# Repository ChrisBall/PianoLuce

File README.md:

# PianoLuce

PianoLuce is a keypress detector for pianos, based on the Arduino platform. This project is on hiatus, having achieved it's main aim, but others trying to achieve similar results may find these resources useful.

This project took inspiration from the development on the [Magnetic Resonator Piano](http://www.eecs.qmul.ac.uk/~andrewm/mrp.html) and similar, commercial keypress detectors like the Moog Piano Bar.

Most of the development was in aid of a performance by Marta Mołodyńska-Wheeler in June 2017, where live visuals were generated from her PhD performance of Scriabin's 24 preludes. The vision of the project was to re-create a modern day version of [Clavier à lumières](https://en.wikipedia.org/wiki/Clavier_%C3%A0_lumi%C3%A8res) by creating a non-intrusive device which could be attached to an expensive piano and create colored visuals.  Alex (Marta's husband), CEO of the IOT company [Kolomolo](www.kolomolo.com), connected with me during his research and commissioned the work.

My special thanks to: [Alex & Marta](http://www.martamolo.com/), for their time, patience, and escape rooms; to [James Medd](http://jamesmedd.co.uk/) for his assistance designing a mounting system, and coming up with the name, PianoLuce; and to [Alexander Lang](http://langster1980.blogspot.co.uk/), for his usual excellent support.

## Description

PianoLuce uses side-mounted IR reflection detectors to estimate the velocity of keypresses. An IR reflection sensor (QRE1113) above each key measures reflected IR light. These sensors are switched on and read in sequence by an ATMEGA328P via 16 channel 4067 analog multiplexers. Each PCB spans an octave (12 notes), and boards communicate via I2C, although SPI may be possible. A master controller is responsible for controlling calibration, receiving keypress data from each slave board, getting data from a sustain pedal, and sending midi over USB.

## Resources
- [Arduino Code](https://github.com/ChrisBall/PianoLuce/tree/master/Arduino)
- [Eagle Files](https://github.com/ChrisBall/PianoLuce/tree/master/Eagle)
- [Mount design and cad files](https://github.com/ChrisBall/PianoLuce/tree/master/SVG)
- [Other Media](https://github.com/ChrisBall/PianoLuce/tree/master/Media)

## Flaws and possible improvements

As mentioned, PianoLuce is only partially developed, and there are many factors to consider in an improved future version. Please bear these points in mind before using this project as a basis for your own.
- Currently, keypresses on black keys are detected with ambient IR, which is obviously highly variable. More reliable measurement can be made by adding white stickers to each black key, and altering the current code to light the appropriate IR LED. A simpler to install system may use two reflection sensors to sense the void left by the black key when it is pressed.
- I2C is not designed for long range transmission: although the current system works (multi-slave setup), it may be susceptible to noise, and there is significant latency introduced by evaluating 7 slave boards. Improved data transmission between master and slaves should be implemented.
- The electronic design, while functional, could be simplified, made cheaper and smaller, and use a faster microcontroller from the STM32 series.
- The 10 pin IDC connectors chosen for board interconnects may disturb the performance of experienced pianists, particularly those with smaller hands as they will use the full length of each key. A lower profile interconnect would be ideal.
- There is no visual feedback: this was intentional, as it was deemed undesirable for our purposes, but in most cases it should be an option. LED feedback for each key is simple to add.

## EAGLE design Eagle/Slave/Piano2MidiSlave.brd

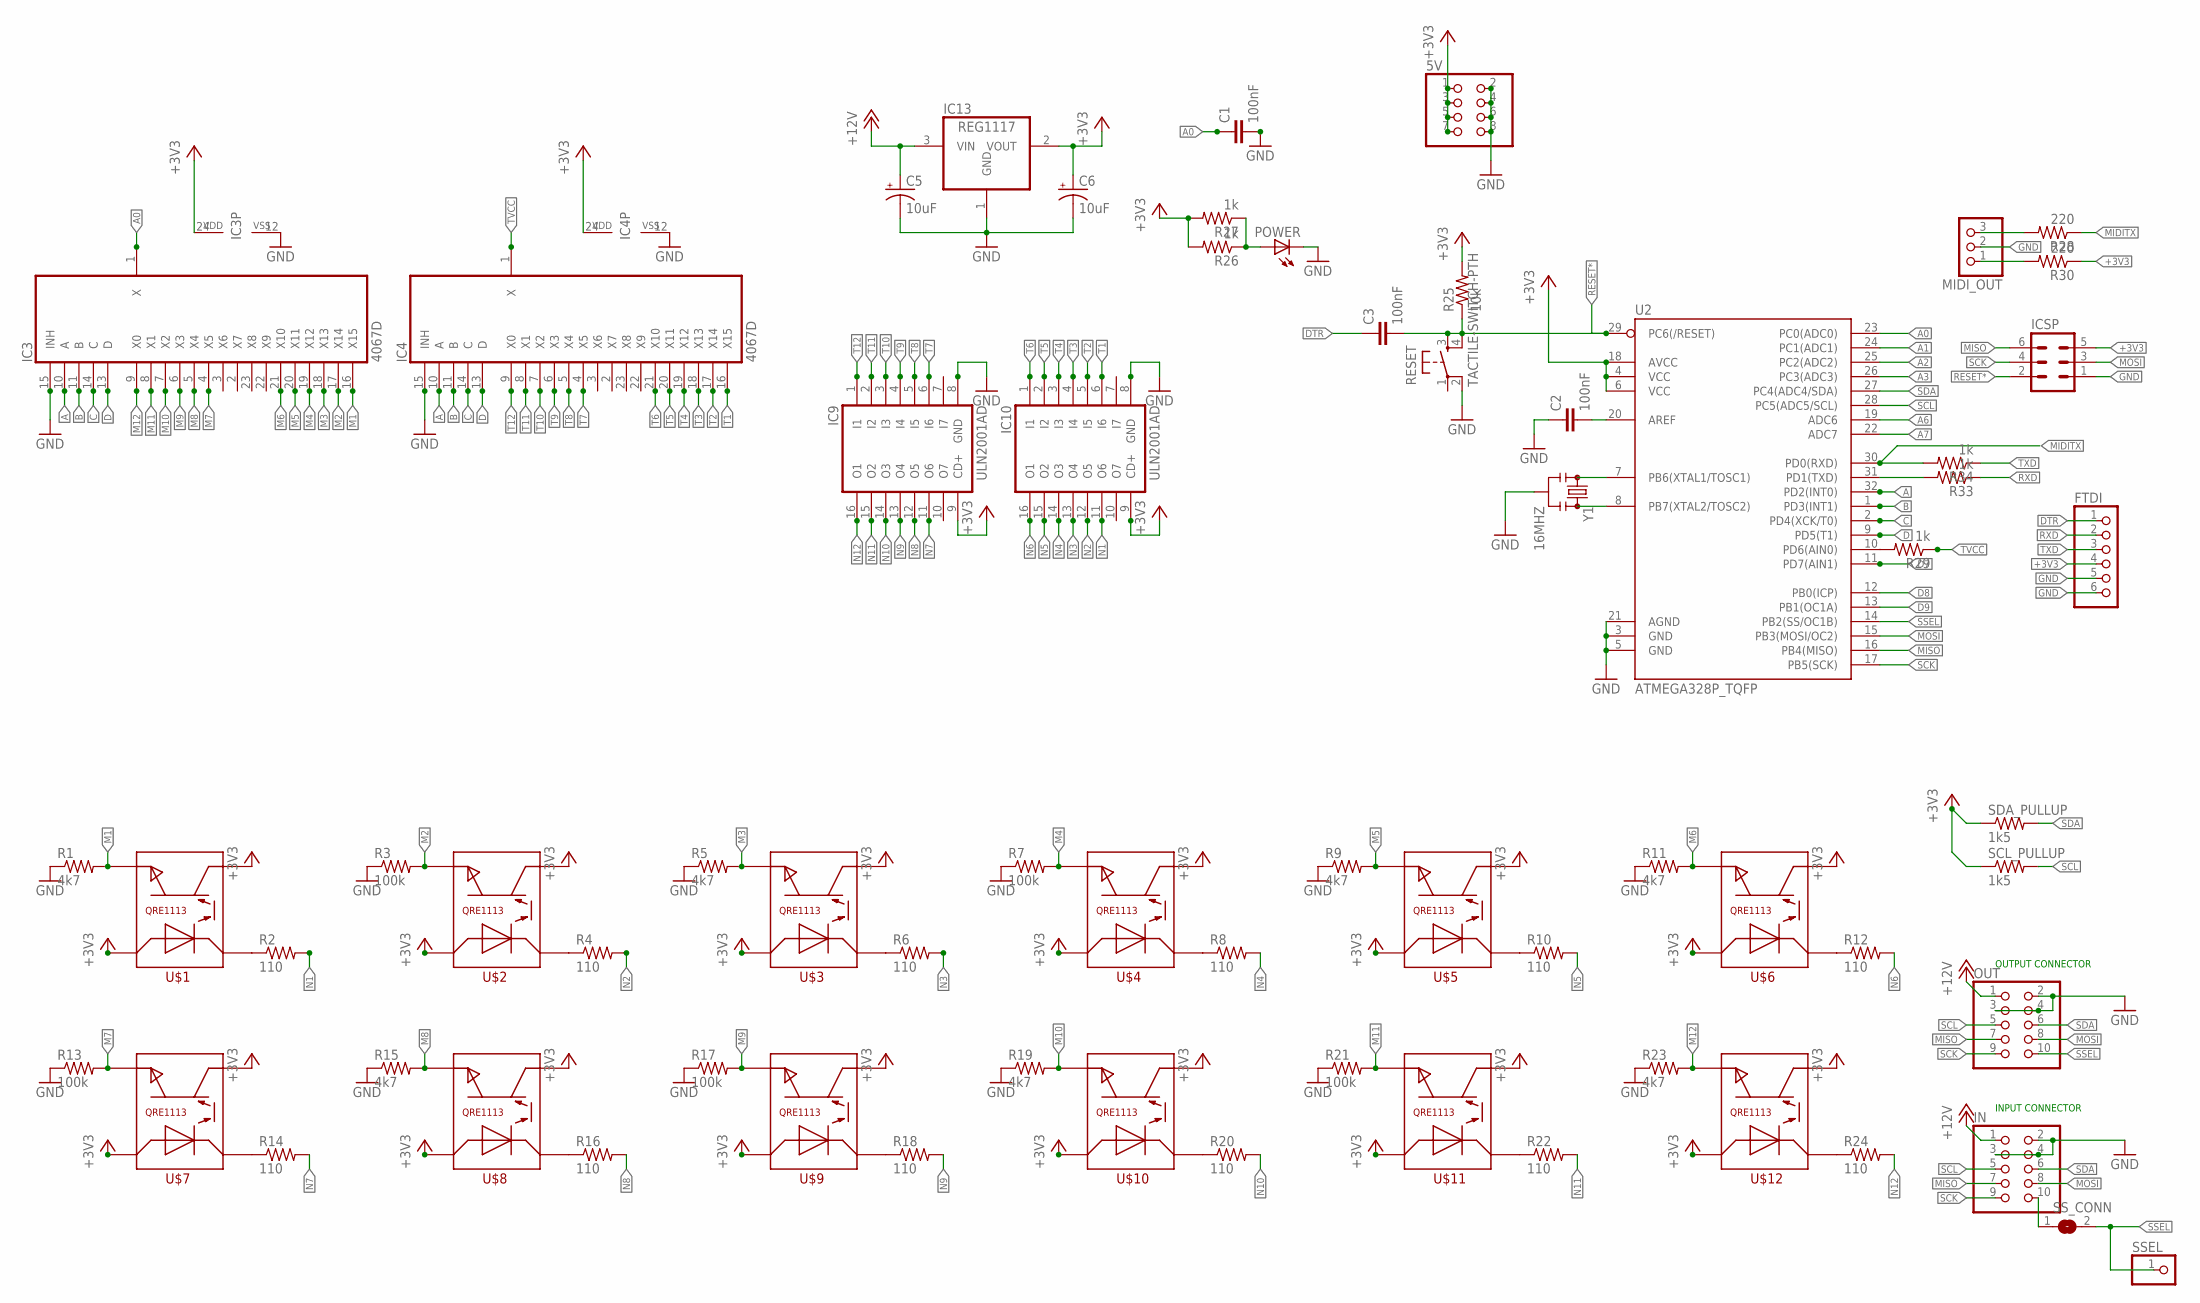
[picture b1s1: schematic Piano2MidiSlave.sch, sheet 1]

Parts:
5V: PINHD-2X4; 2X04
C1, C2, C3: 100nF; C0805
C5, C6: 10uF; SMC_A
FTDI: PINHD-1X6; 1X06
IC3, IC4: 4067D; SO24W
IC9, IC10: ULN2001AD; SO16
IC13: REG1117; SOT223
ICSP: MA03-2
IN: PINHD-2X5IDC; 2X05IDC
MIDI_OUT: PINHD-1X3; 1X03
OUT: PINHD-2X5IDC; 2X05IDC
POWER: LEDCHIPLED_0805; CHIPLED_0805
R1, R5, R9, R11, R15, R19, R23: 4k7; M0805
R2, R4, R6, R8, R10, R12, R14, R16, R18, R20, R22, R24: 110; M0805
R3, R7, R13, R17, R21: 100k; M0805
R25: 10k; M0805
R26, R27, R29, R33, R34: 1k; M0805
R28, R30: 220; M0805
RESET: TACTILE-SWITCH-PTH; TAC-SWITCH-PTH
SCL_PULLUP: 1k5; M0805
SDA_PULLUP: 1k5; M0805
SSEL: PINHD-1X1; 1X01
SS_CONN: SJ
U2: ATMEGA328P_TQFP; TQFP32-08
U$1, U$2, U$3, U$4, U$5, U$6, U$7, U$8, U$9, U$10, U$11, U$12: QRE1113QRE1113; QRE1113
Y1: 16MHZ; RESONATOR-SMD

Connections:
+3V3: 5V.1, 5V.3, 5V.5, 5V.7, C6.+, FTDI.4 (SDA), IC3.24 (VDD), IC4.24 (VDD), IC9.9 (CD+), IC10.9 (CD+), IC13.2 (VOUT), ICSP.5, R25.2, R26.2, R27.2, R30.1, SCL_PULLUP.1, SDA_PULLUP.1, U2.4 (VCC), U2.6 (VCC), U2.18 (AVCC), U$1.ANODE, U$1.COLLECTOR, U$2.ANODE, U$2.COLLECTOR, U$3.ANODE, U$3.COLLECTOR, U$4.ANODE, U$4.COLLECTOR, U$5.ANODE, U$5.COLLECTOR, U$6.ANODE, U$6.COLLECTOR, U$7.ANODE, U$7.COLLECTOR, U$8.ANODE, U$8.COLLECTOR, U$9.ANODE, U$9.COLLECTOR, U$10.ANODE, U$10.COLLECTOR, U$11.ANODE, U$11.COLLECTOR, U$12.ANODE, U$12.COLLECTOR
+12V: C5.+, IC13.3 (VIN), IN.1, OUT.1
A: IC3.10 (A), IC4.10 (A), U2.32 (PD2(INT0))
A0: C1.1, IC3.1 (X), U2.23 (PC0(ADC0))
A1: U2.24 (PC1(ADC1))
A2: U2.25 (PC2(ADC2))
A3: U2.26 (PC3(ADC3))
A6: U2.19 (ADC6)
A7: U2.22 (ADC7)
AREF: C2.2, U2.20 (AREF)
B: IC3.11 (B), IC4.11 (B), U2.1 (PD3(INT1))
C: IC3.14 (C), IC4.14 (C), U2.2 (PD4(XCK/T0))
D: IC3.13 (D), IC4.13 (D), U2.9 (PD5(T1))
D7: U2.11 (PD7(AIN1))
D8: U2.12 (PB0(ICP))
D9: U2.13 (PB1(OC1A))
DTR: C3.1, FTDI.1 (3V3)
GND: 5V.2, 5V.4, 5V.6, 5V.8, C1.2, C2.1, C5.-, C6.-, FTDI.5 (ADD), FTDI.6 (GND), IC3.12 (VSS), IC3.15 (INH), IC4.12 (VSS), IC4.15 (INH), IC9.8 (GND), IC10.8 (GND), IC13.1 (GND), ICSP.1, IN.2, IN.3, IN.4, MIDI_OUT.2, OUT.2, OUT.3, OUT.4, POWER.C, R1.1, R3.1, R5.1, R7.1, R9.1, R11.1, R13.1, R15.1, R17.1, R19.1, R21.1, R23.1, RESET.2, U2.3 (GND), U2.5 (GND), U2.21 (AGND), Y1.2
M1: IC3.16 (X15), R1.2, U$1.EMITTER
M2: IC3.17 (X14), R3.2, U$2.EMITTER
M3: IC3.18 (X13), R5.2, U$3.EMITTER
M4: IC3.19 (X12), R7.2, U$4.EMITTER
M5: IC3.20 (X11), R9.2, U$5.EMITTER
M6: IC3.21 (X10), R11.2, U$6.EMITTER
M7: IC3.4 (X5), R13.2, U$7.EMITTER
M8: IC3.5 (X4), R15.2, U$8.EMITTER
M9: IC3.6 (X3), R17.2, U$9.EMITTER
M10: IC3.7 (X2), R19.2, U$10.EMITTER
M11: IC3.8 (X1), R21.2, U$11.EMITTER
M12: IC3.9 (X0), R23.2, U$12.EMITTER
MIDITX: R28.1, R34.2, U2.30 (PD0(RXD))
MISO: ICSP.6, IN.7, OUT.7, U2.16 (PB4(MISO))
MOSI: ICSP.3, IN.8, OUT.8, U2.15 (PB3(MOSI/OC2))
N1: IC10.11 (O6), R2.2
N2: IC10.12 (O5), R4.2
N3: IC10.13 (O4), R6.2
N4: IC10.14 (O3), R8.2
N5: IC10.15 (O2), R10.2
N6: IC10.16 (O1), R12.2
N7: IC9.11 (O6), R14.2
N8: IC9.12 (O5), R16.2
N9: IC9.13 (O4), R18.2
N10: IC9.14 (O3), R20.2
N11: IC9.15 (O2), R22.2
N12: IC9.16 (O1), R24.2
unnamed: U2.8 (PB7(XTAL2/TOSC2)), Y1.3
unnamed: U2.7 (PB6(XTAL1/TOSC1)), Y1.1
unnamed: R4.1, U$2.CATHODE
unnamed: R6.1, U$3.CATHODE
unnamed: MIDI_OUT.3, R28.2
unnamed: R2.1, U$1.CATHODE
unnamed: POWER.A, R26.1, R27.1
unnamed: R8.1, U$4.CATHODE
unnamed: R29.2, U2.10 (PD6(AIN0))
unnamed: R10.1, U$5.CATHODE
unnamed: R12.1, U$6.CATHODE
unnamed: R24.1, U$12.CATHODE
unnamed: R33.2, U2.31 (PD1(TXD))
unnamed: R22.1, U$11.CATHODE
unnamed: R20.1, U$10.CATHODE
unnamed: R18.1, U$9.CATHODE
unnamed: R16.1, U$8.CATHODE
unnamed: R14.1, U$7.CATHODE
unnamed: IN.10, SS_CONN.1
unnamed: MIDI_OUT.1, R30.2
RESET*: C3.2, ICSP.2, R25.1, RESET.3, RESET.4, U2.29 (PC6(/RESET))
RXD: FTDI.2 (IRQ), R33.1
SCK: ICSP.4, IN.9, OUT.9, U2.17 (PB5(SCK))
SCL: IN.5, OUT.5, SCL_PULLUP.2, U2.28 (PC5(ADC5/SCL))
SDA: IN.6, OUT.6, SDA_PULLUP.2, U2.27 (PC4(ADC4/SDA))
SSEL: OUT.10, SSEL.1, SS_CONN.2, U2.14 (PB2(SS/OC1B))
T1: IC4.16 (X15), IC10.6 (I6)
T2: IC4.17 (X14), IC10.5 (I5)
T3: IC4.18 (X13), IC10.4 (I4)
T4: IC4.19 (X12), IC10.3 (I3)
T5: IC4.20 (X11), IC10.2 (I2)
T6: IC4.21 (X10), IC10.1 (I1)
T7: IC4.4 (X5), IC9.6 (I6)
T8: IC4.5 (X4), IC9.5 (I5)
T9: IC4.6 (X3), IC9.4 (I4)
T10: IC4.7 (X2), IC9.3 (I3)
T11: IC4.8 (X1), IC9.2 (I2)
T12: IC4.9 (X0), IC9.1 (I1)
TVCC: IC4.1 (X), R29.1
TXD: FTDI.3 (SCL), R34.1

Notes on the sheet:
INPUT CONNECTOR
OUTPUT CONNECTOR

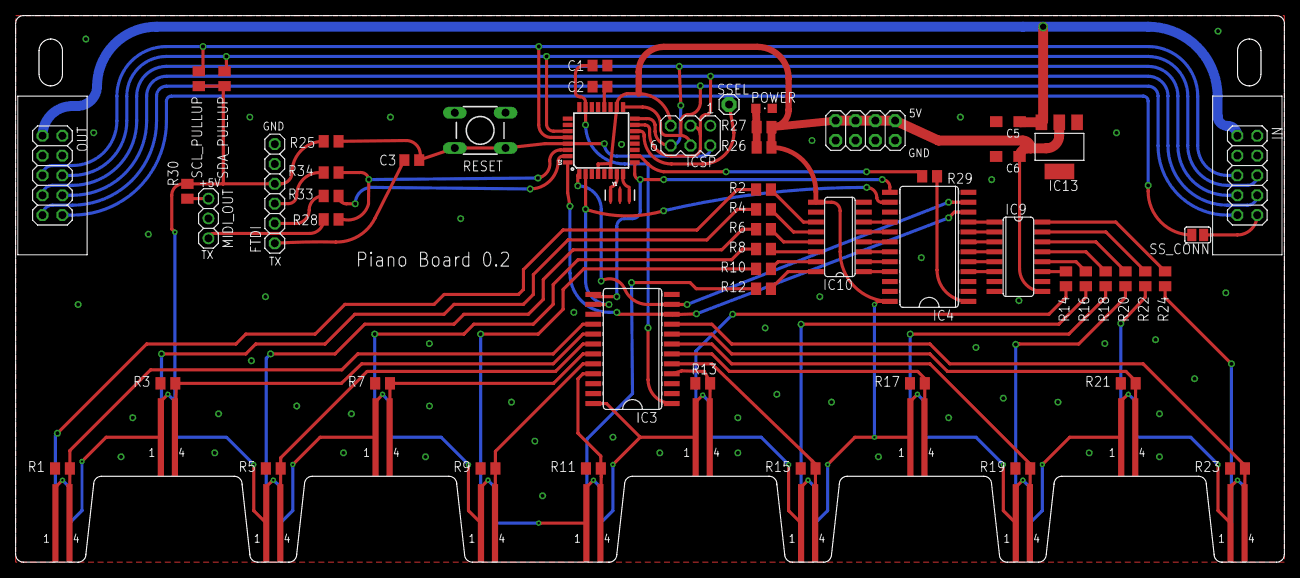
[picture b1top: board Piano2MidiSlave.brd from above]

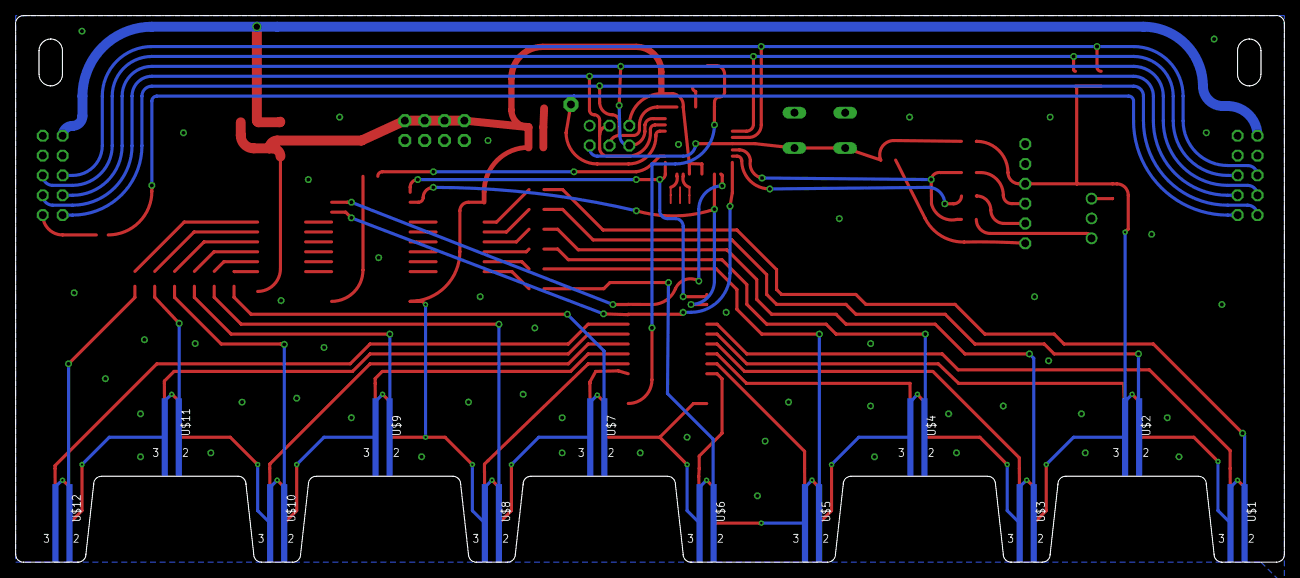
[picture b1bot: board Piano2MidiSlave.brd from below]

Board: 2 copper layers, 162.5 x 70.0 mm, 68 parts (12 on the bottom side), 77 nets.

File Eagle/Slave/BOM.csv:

"Qty";"Value";"Device";"Package";"Parts";"Description";"MF";"MPN";"OC_FARNELL";"OC_NEWARK";"PROD_ID";"SPICEMODEL";"SPICEPREFIX";"VALUE";
"1";"";"LEDCHIPLED_0805";"CHIPLED_0805";"POWER";"LED";"";"";"";"";"";"";"";"";
"1";"";"MA03-2";"MA03-2";"ICSP";"PIN HEADER";"";"";"unknown";"unknown";"";"";"";"";
"1";"";"PINHD-1X1";"1X01";"SSEL";"Pin header 1x1 for 0.1" spacing";"";"";"";"";"";"";"";"";
"1";"";"PINHD-1X3";"1X03";"MIDI_OUT";"PIN HEADER";"";"";"";"";"";"";"";"";
"1";"";"PINHD-1X6";"1X06";"FTDI";"PIN HEADER";"";"";"";"";"";"";"";"";
"1";"";"PINHD-2X4";"2X04";"5V";"PIN HEADER";"";"";"";"";"";"";"";"";
"2";"";"PINHD-2X5IDC";"2X05IDC";"IN, OUT";"PIN HEADER";"";"";"";"";"";"";"";"";
"1";"";"SJ";"SJ";"SS_CONN";"SMD solder JUMPER";"";"";"";"";"";"";"";"";
"5";"100k";"R-US_M0805";"M0805";"R3, R7, R13, R17, R21";"RESISTOR, American symbol";"";"";"";"";"";"";"";"";
"3";"100nF";"C";"C0805";"C1, C2, C3";"CAPACITOR, European symbol";"";"";"";"";"";"NONE";"C";"";
"1";"10k";"R-US_M0805";"M0805";"R25";"RESISTOR, American symbol";"";"";"";"";"";"";"";"";
"2";"10uF";"CPOL-USSMCA";"SMC_A";"C5, C6";"POLARIZED CAPACITOR, American symbol";"";"";"";"";"";"";"";"";
"12";"110";"R-US_M0805";"M0805";"R2, R4, R6, R8, R10, R12, R14, R16, R18, R20, R22, R24";"RESISTOR, American symbol";"";"";"";"";"";"";"";"";
"1";"16MHZ";"RESONATOR8MHZ";"RESONATOR-SMD";"Y1";"Resonator";"";"";"";"";"XTAL-08895";"";"";"8MHZ";
"5";"1k";"R-US_M0805";"M0805";"R26, R27, R29, R33, R34";"RESISTOR, American symbol";"";"";"";"";"";"";"";"";
"2";"1k5";"R-US_M0805";"M0805";"SCL_PULLUP, SDA_PULLUP";"RESISTOR, American symbol";"";"";"";"";"";"";"";"";
"2";"220";"R-US_M0805";"M0805";"R28, R30";"RESISTOR, American symbol";"";"";"";"";"";"";"";"";
"2";"4067D";"4067D";"SO24W";"IC3, IC4";"16-channel ANALOG MULTIPLEXER";"";"";"";"";"";"";"";"";
"7";"4k7";"R-US_M0805";"M0805";"R1, R5, R9, R11, R15, R19, R23";"RESISTOR, American symbol";"";"";"";"";"";"";"";"";
"1";"ATMEGA328P_TQFP";"ATMEGA328P_TQFP";"TQFP32-08";"U2";"";"";"";"";"";"IC-09069";"";"";"ATMEGA328P_TQFP";
"12";"QRE1113QRE1113";"QRE1113QRE1113";"QRE1113";"U$1, U$2, U$3, U$4, U$5, U$6, U$7, U$8, U$9, U$10, U$11, U$12";"";"";"";"";"";"";"";"";"";
"1";"REG1117";"REG1117";"SOT223";"IC13";"800mA and 1A Low Dropout (LDO) Positive Regulator";"";"REG1117";"1097566";"14P6981";"";"";"";"";
"1";"TACTILE-SWITCH-PTH";"TACTILE-SWITCH-PTH";"TAC-SWITCH-PTH";"RESET";"Tactile Switch 4 Pins, SPST NO";"";"";"";"";"";"";"";"";
"2";"ULN2001AD";"ULN2001AD";"SO16";"IC9, IC10";"DRIVER ARRAY";"";"";"";"";"";"";"";"";

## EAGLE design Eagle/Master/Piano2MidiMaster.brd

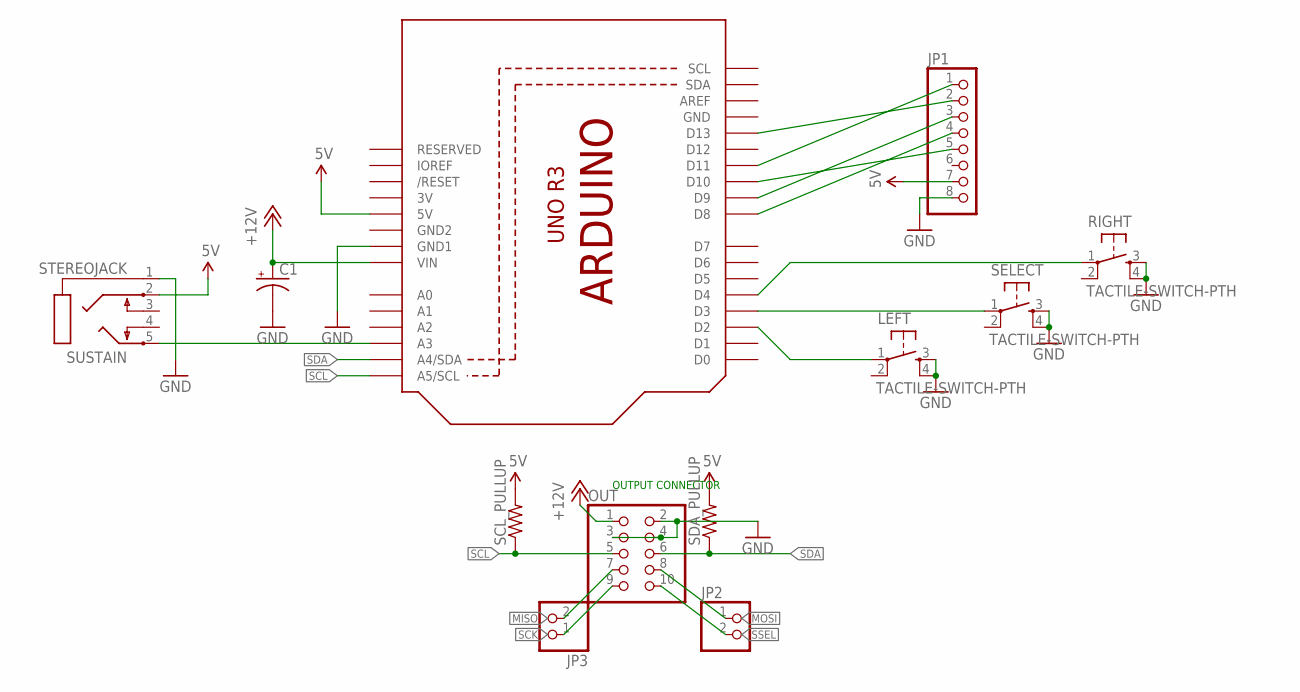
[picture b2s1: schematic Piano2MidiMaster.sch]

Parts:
C1: CPOL-USE2.5-6; E2,5-6
JP1: PINHD-1X8BIG; 1X08-BIG
JP2, JP3: PINHD-1X2; 1X02
LEFT: TACTILE-SWITCH-PTH; TAC-SWITCH-PTH
OUT: PINHD-2X5IDC; 2X05IDC
RIGHT: TACTILE-SWITCH-PTH; TAC-SWITCH-PTH
SCL_PULLUP: R-US_0207/15; 0207/15
SDA_PULLUP: R-US_0207/12; 0207/12
SELECT: TACTILE-SWITCH-PTH; TAC-SWITCH-PTH
SUSTAIN: STEREOJACK; STX3100
U1: ARDUINOR3-DIMENSION; ARDUINOR3

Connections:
3V: U1.3V
5V: JP1.7, SCL_PULLUP.2, SDA_PULLUP.2, SUSTAIN.2, U1.5V
+12V: C1.+, OUT.1, U1.VIN
GND: C1.-, JP1.8, LEFT.3, LEFT.4, OUT.2, OUT.3, OUT.4, RIGHT.3, RIGHT.4, SELECT.3, SELECT.4, SUSTAIN.1, U1.GND, U1.GND1
GND2: U1.GND2
MISO: JP3.2, OUT.7
MOSI: JP2.1, OUT.8
unnamed: JP1.1, U1.D11
unnamed: JP1.2, U1.D13
unnamed: JP1.3, U1.D9
unnamed: JP1.4, U1.D8
unnamed: JP1.5, U1.D10
unnamed: LEFT.1, U1.D2
unnamed: SELECT.1, U1.D3
unnamed: RIGHT.1, U1.D4
unnamed: SUSTAIN.5, U1.A3
SCK: JP3.1, OUT.9
SCL: OUT.5, SCL_PULLUP.1, U1.A5 (A5/SCL)
SDA: OUT.6, SDA_PULLUP.1, U1.A4 (A4/SDA)
SSEL: JP2.2, OUT.10

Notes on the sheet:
OUTPUT CONNECTOR

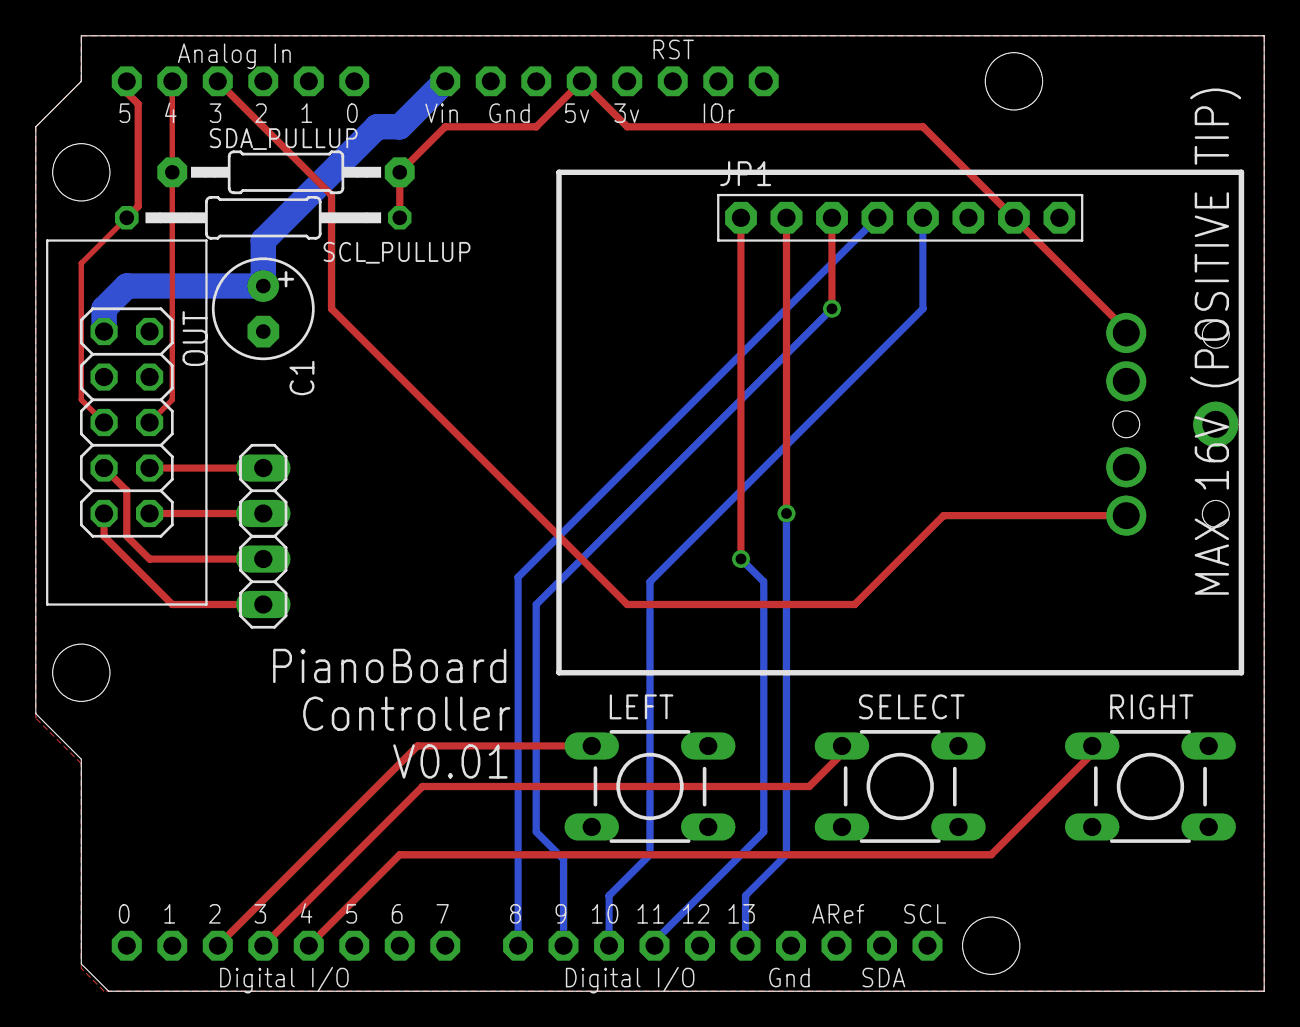
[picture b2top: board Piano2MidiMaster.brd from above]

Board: 2 copper layers, 68.6 x 53.3 mm, 12 parts (1 on the bottom side), 18 nets.

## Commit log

2018-02-07 Set theme jekyll-theme-slate
2018-02-07 test
    initial commit
2018-02-07 added basic copy
2018-02-07 Fodler creation
2018-02-07 further copy
2018-02-07 headings
2018-02-07 populated most files
    Added eagle files, arduino files, added further copy and CAD files
2018-02-07 added links
2018-02-07 Added links
    but better this time
2018-02-07 Tidied formatting
2018-02-07 Added photos from installation
2018-02-07 improved formatting
2018-02-07 Minor changes
2018-02-07 Added one more photo
2018-02-07 Added main photo
2018-02-07 Image formatting
2018-02-07 jekyll images
2018-02-07 added more links
2018-02-07 filename change
2018-02-08 edit copy

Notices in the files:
parts and their libraries:
GeekAmmo: Licensing:Creative Commons ShareAlike 4.0 International - https://creativecommons.org/licenses/by-sa/4.0
